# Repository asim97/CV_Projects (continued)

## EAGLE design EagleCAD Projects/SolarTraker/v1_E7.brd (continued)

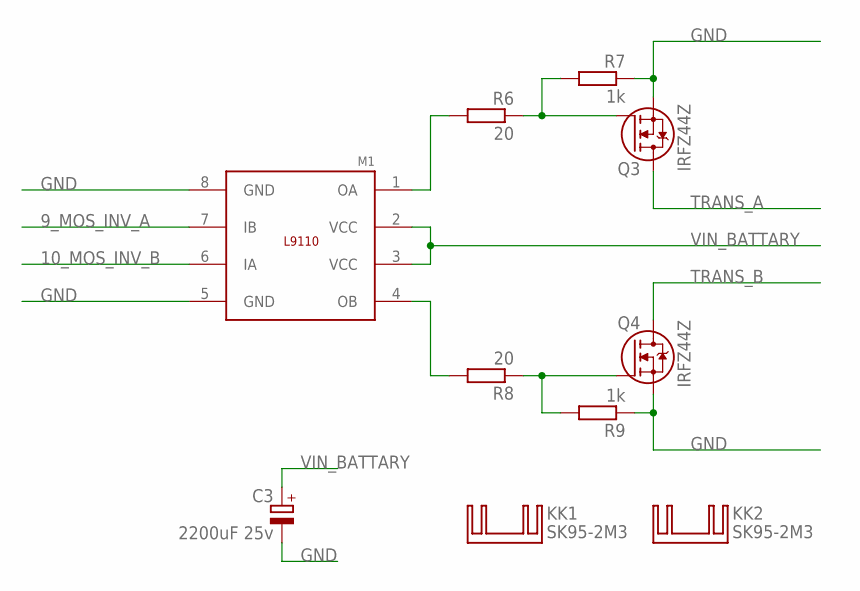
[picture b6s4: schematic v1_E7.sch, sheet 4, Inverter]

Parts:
C3: 2200uF 25v; E5-13
KK1, KK2: SK95-2M3
M1: L9110; SO8P
Q3, Q4: IRFZ44Z; TO220V
R6, R8: 20; 0207/10
R7, R9: 1k; 0207/10

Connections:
9_MOS_INV_A: M1.7 (IB); also elsewhere on the board
10_MOS_INV_B: M1.6 (IA); also elsewhere on the board
GND: C3.-, M1.5 (GND), M1.8 (GND), Q3.3 (S), Q4.3 (S), R7.1, R9.1; also elsewhere on the board
unnamed: Q3.1 (G), R6.1, R7.2
unnamed: M1.4 (OB), R8.2
unnamed: Q4.1 (G), R8.1, R9.2
unnamed: M1.1 (OA), R6.2
TRANS_A: Q3.2 (D); also elsewhere on the board
TRANS_B: Q4.2 (D); also elsewhere on the board
VIN_BATTARY: C3.+, M1.2 (VCC), M1.3 (VCC); also elsewhere on the board

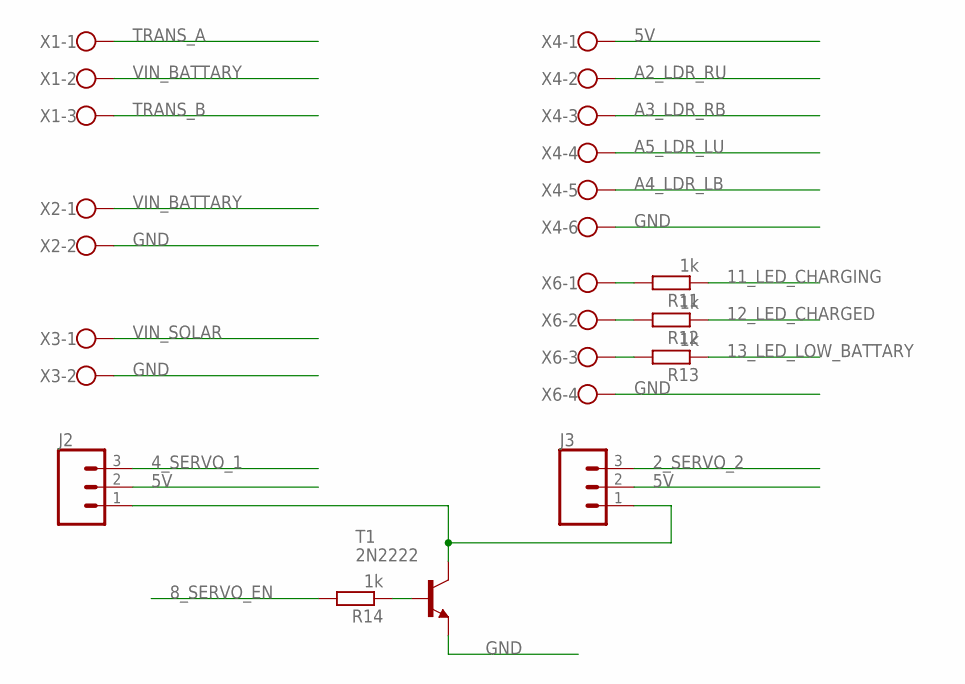
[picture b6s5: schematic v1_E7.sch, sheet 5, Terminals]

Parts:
J2, J3: CONN_03JST-PTH-VERT; JST-3-PTH-VERT
R11, R12, R13, R14: 1k; 0207/10
T1: 2N2222; TO92-EBC-OVAL
X1: W237-103
X2, X3: W237-102
X4: W237-6
X6: W237-4

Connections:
2_SERVO_2: J3.3; also elsewhere on the board
4_SERVO_1: J2.3; also elsewhere on the board
5V: J2.2, J3.2, X4.1; also elsewhere on the board
8_SERVO_EN: R14.2; also elsewhere on the board
11_LED_CHARGING: R11.1; also elsewhere on the board
12_LED_CHARGED: R12.1; also elsewhere on the board
13_LED_LOW_BATTARY: R13.1; also elsewhere on the board
A2_LDR_RU: X4.2; also elsewhere on the board
A3_LDR_RB: X4.3; also elsewhere on the board
A4_LDR_LB: X4.5; also elsewhere on the board
A5_LDR_LU: X4.4; also elsewhere on the board
GND: T1.E, X2.2, X3.2, X4.6, X6.4; also elsewhere on the board
unnamed: R13.2, X6.3
unnamed: R12.2, X6.2
unnamed: R11.2, X6.1
unnamed: R14.1, T1.B
unnamed: J2.1, J3.1, T1.C
TRANS_A: X1.1; also elsewhere on the board
TRANS_B: X1.3; also elsewhere on the board
VIN_BATTARY: X1.2, X2.1; also elsewhere on the board
VIN_SOLAR: X3.1; also elsewhere on the board

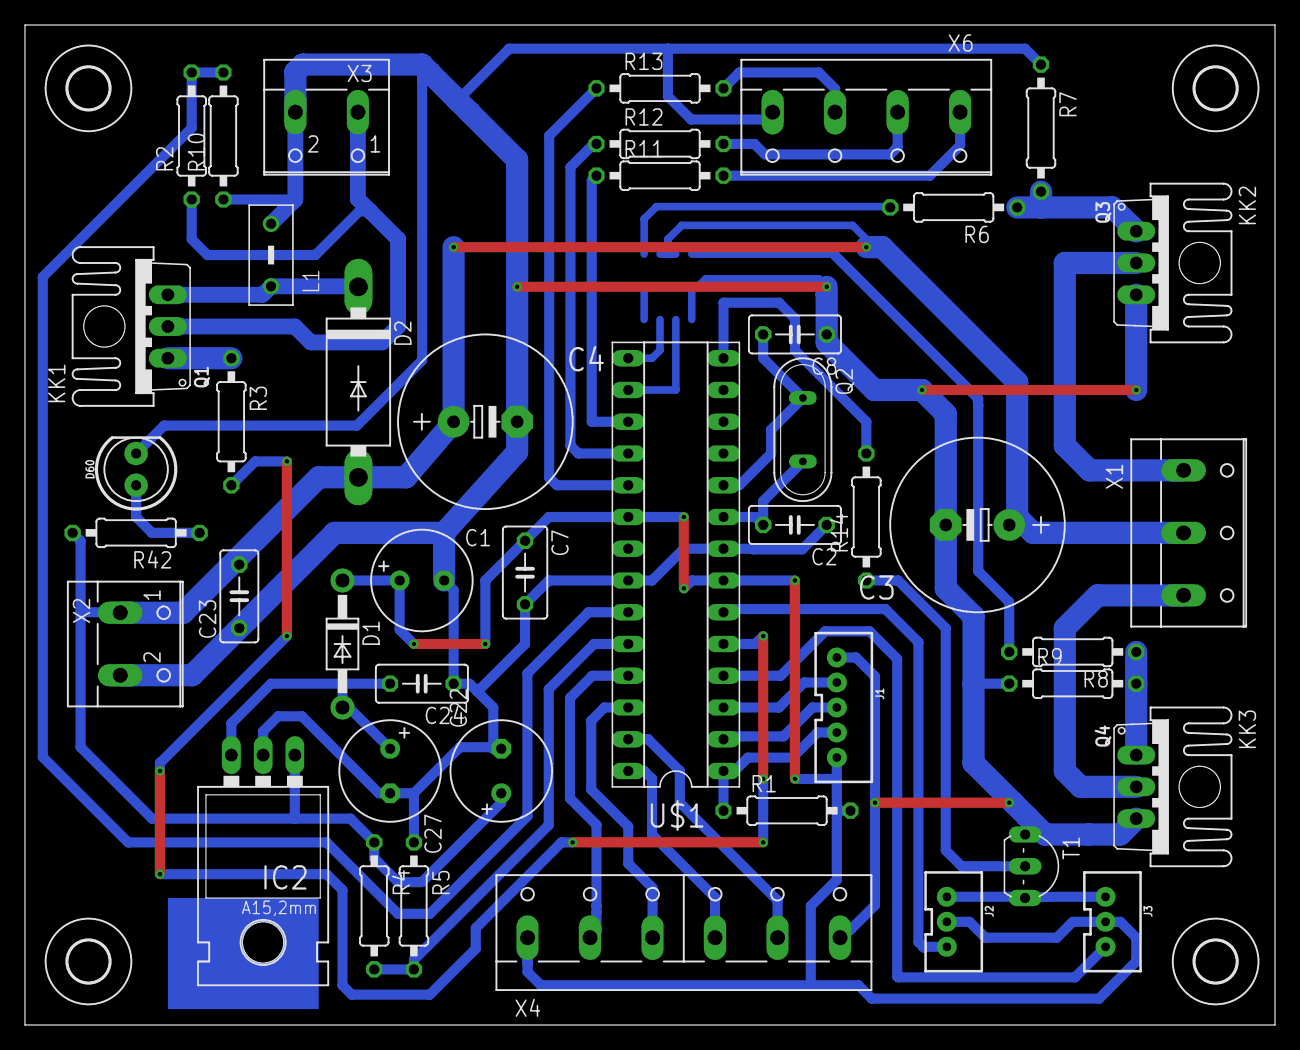
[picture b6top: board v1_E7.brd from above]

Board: 2 copper layers, 100.0 x 80.0 mm, 52 parts (1 on the bottom side), 39 nets.

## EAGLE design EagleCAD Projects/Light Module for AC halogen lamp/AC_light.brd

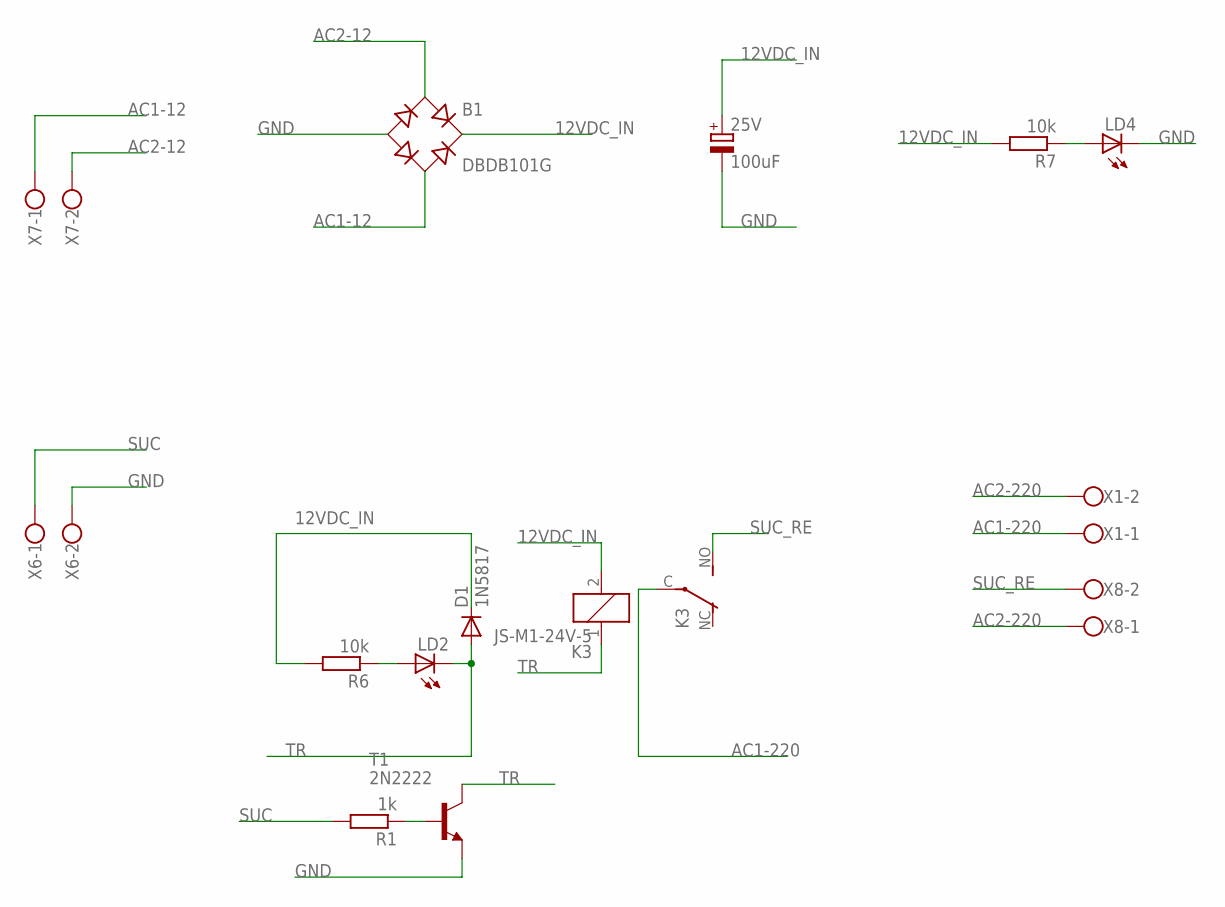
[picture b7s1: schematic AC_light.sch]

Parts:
25V: 100uF; E3,5-8
B1: DBDB101G; DB
D1: 1N5817; DO41-10
K3: JS-M1-24V-5; JS-M
LD2, LD4: LED5MM
R1: 1k; 0207/10
R6, R7: 10k; 0207/10
T1: 2N2222; TO92-EBC-OVAL
X1, X6, X7, X8: W237-102

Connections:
12VDC_IN: 25V.+, B1.+, D1.C, K3.2, R6.2, R7.2
AC1-12: B1.AC2, X7.1
AC1-220: K3.C, X1.1
AC2-12: B1.AC1, X7.2
AC2-220: X1.2, X8.1
GND: 25V.-, B1.-, LD4.K (C), T1.E, X6.2
unnamed: R1.1, T1.B
unnamed: LD4.A, R7.1
unnamed: LD2.A, R6.1
SUC: R1.2, X6.1
SUC_RE: K3.NO (S), X8.2
TR: D1.A, K3.1, LD2.K (C), T1.C

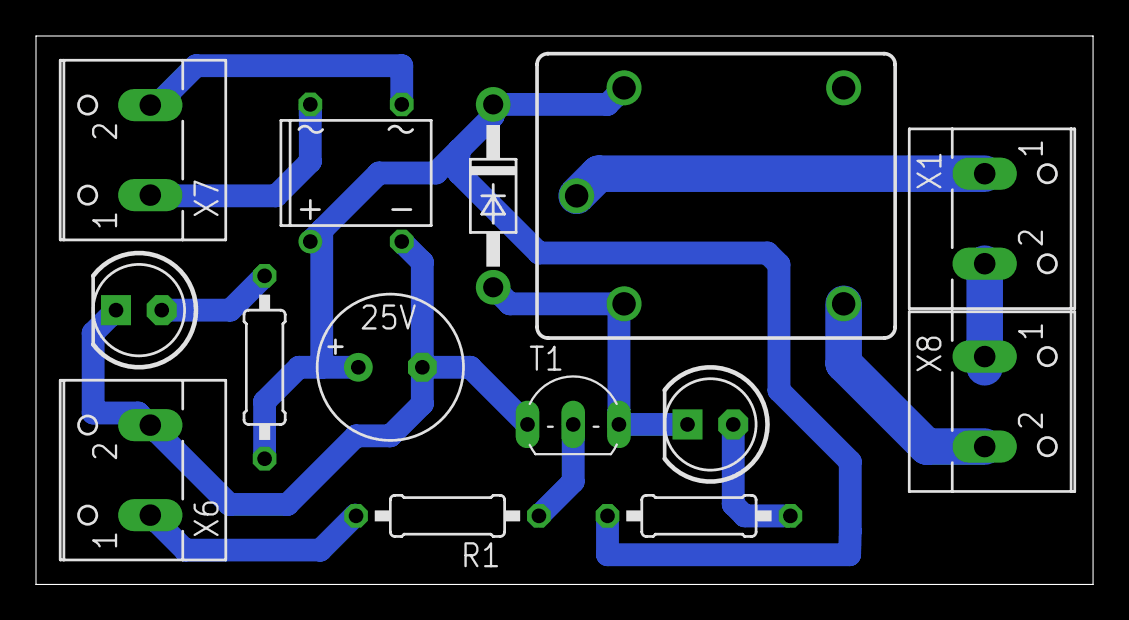
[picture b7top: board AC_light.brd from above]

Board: 2 copper layers, 58.7 x 30.5 mm, 14 parts (0 on the bottom side), 12 nets.

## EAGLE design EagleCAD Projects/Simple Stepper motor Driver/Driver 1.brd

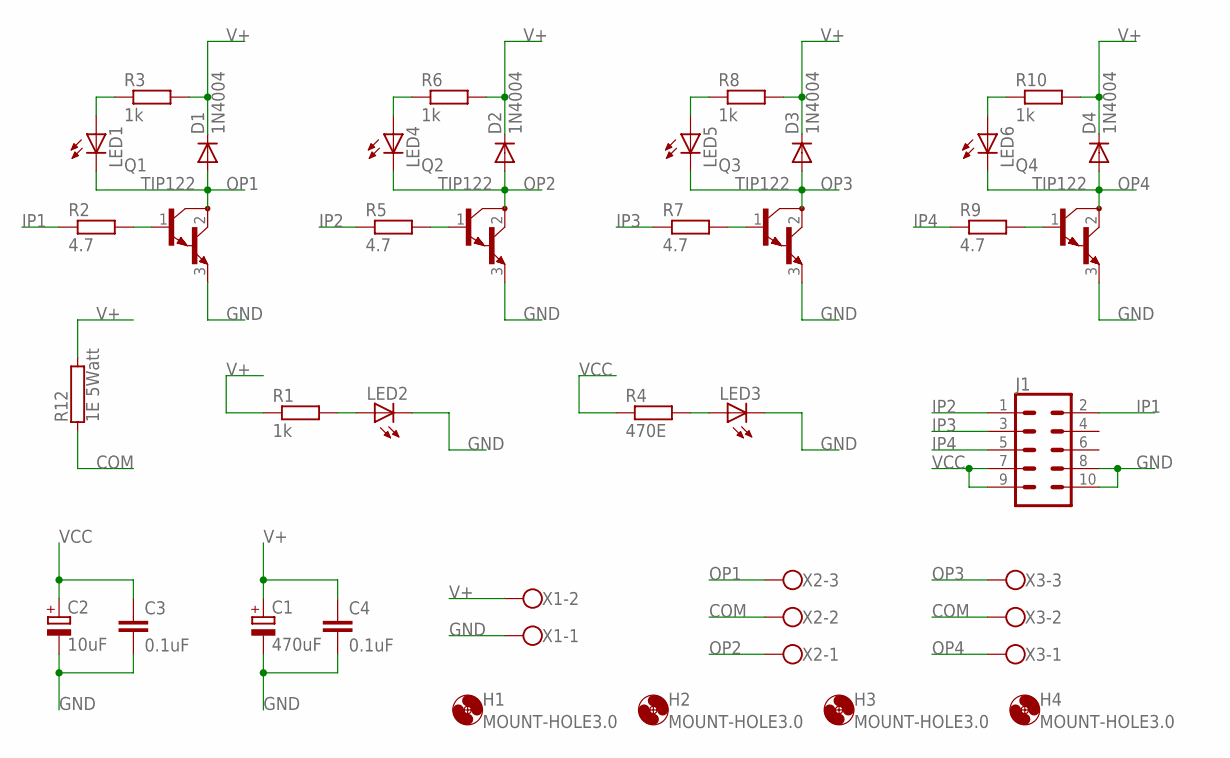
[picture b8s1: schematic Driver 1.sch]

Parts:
C1: 470uF; E5-8,5
C2: 10uF; E2-5
C3, C4: 0.1uF; C025-025X050
D1, D2, D3, D4: 1N4004; DO41-10
H1, H2, H3, H4: MOUNT-HOLE3.0; 3,0
J1: CONN_05X2RAF; 2X5-RAF
LED1, LED2, LED3, LED4, LED5, LED6: LED5MM
Q1, Q2, Q3, Q4: TIP122; TO220
R1, R3, R6, R8, R10: 1k; 0207/10
R2, R5, R7, R9: 4.7; 0207/10
R4: 470E; 0207/10
R12: 1E 5Watt; KH208-8
X1: W237-102
X2, X3: W237-103

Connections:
COM: R12.1, X2.2, X3.2
GND: C1.-, C2.-, C3.2, C4.2, J1.8, J1.10, LED2.K (C), LED3.K (C), Q1.3 (E), Q2.3 (E), Q3.3 (E), Q4.3 (E), X1.1
IP1: J1.2, R2.1
IP2: J1.1, R5.1
IP3: J1.3, R7.1
IP4: J1.5, R9.1
unnamed: LED2.A, R1.2
unnamed: LED1.A, R3.1
unnamed: Q1.1 (B), R2.2
unnamed: LED4.A, R6.1
unnamed: LED3.A, R4.2
unnamed: Q2.1 (B), R5.2
unnamed: LED5.A, R8.1
unnamed: Q3.1 (B), R7.2
unnamed: LED6.A, R10.1
unnamed: Q4.1 (B), R9.2
OP1: D1.A, LED1.K (C), Q1.2 (C), X2.3
OP2: D2.A, LED4.K (C), Q2.2 (C), X2.1
OP3: D3.A, LED5.K (C), Q3.2 (C), X3.3
OP4: D4.A, LED6.K (C), Q4.2 (C), X3.1
V+: C1.+, C4.1, D1.C, D2.C, D3.C, D4.C, R1.1, R3.2, R6.2, R8.2, R10.2, R12.2, X1.2
VCC: C2.+, C3.1, J1.7, J1.9, R4.1

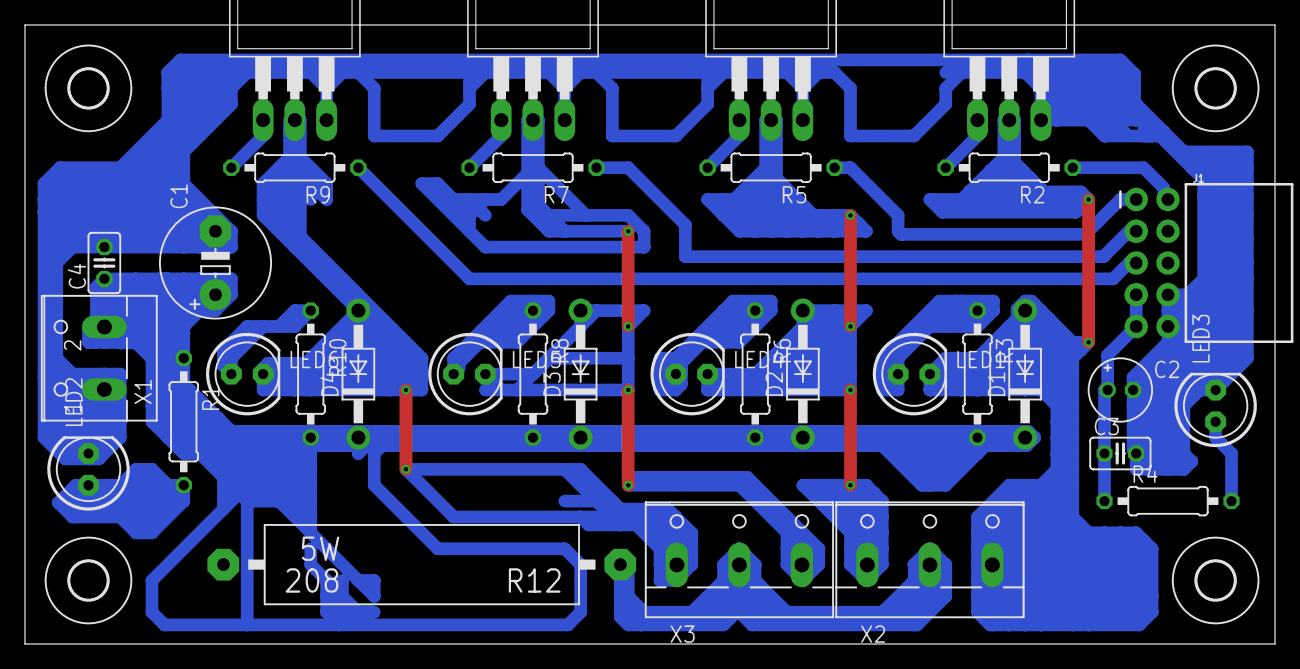
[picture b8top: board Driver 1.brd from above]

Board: 2 copper layers, 100.0 x 49.5 mm, 37 parts (0 on the bottom side), 22 nets.

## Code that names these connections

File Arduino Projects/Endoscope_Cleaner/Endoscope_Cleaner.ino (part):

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bool first_err_scr = true;
bool run_sys = false;

LiquidCrystal lcd(PA3, PD6, PB0, PB1 , PB2, PB3);

//Functions declerd here
void setInputFlags();
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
